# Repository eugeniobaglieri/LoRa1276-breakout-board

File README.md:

# LoRa1276-breakout-board
KiCad schematics and pcb of a breakout board adapter for Nicerf Lora1276 V2.0 - module.

In this Kicad project you will find:
- Nicerf LoRa1276 symbol schematics
- Nicerf LoRa1276 footprint
- Lora Breakout board Adapter schematics
- PCB file
- LORA1276-V2.2 module doc.pdf: Wich contains module specification and measures

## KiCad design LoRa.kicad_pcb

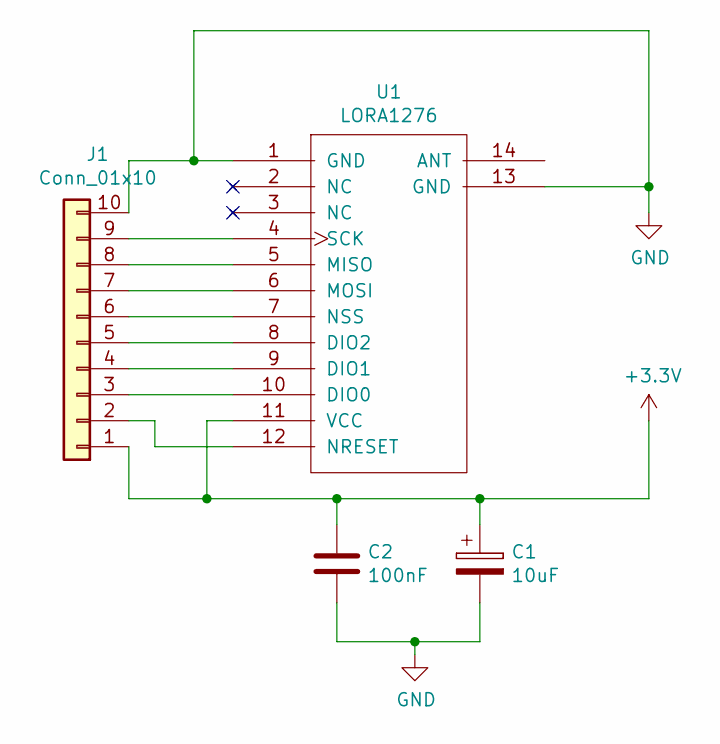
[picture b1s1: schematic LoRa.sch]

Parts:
C1: 10uF; CP_Radial_D5.0mm_P2.50mm
C2: 100nF; C_Disc_D3.8mm_W2.6mm_P2.50mm
J1: Conn_01x10; PinHeader_1x10_P2.54mm_Horizontal
U1: LORA1276

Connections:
+3V3: C1.1, C2.1, J1.1, U1.11 (VCC)
GND: C1.2, C2.2, J1.10, U1.1 (GND), U1.13 (GND)
unnamed: J1.2, U1.12 (NRESET)
unnamed: J1.3, U1.10 (DIO0)
unnamed: J1.4, U1.9 (DIO1)
unnamed: J1.5, U1.8 (DIO2)
unnamed: J1.6, U1.7 (NSS)
unnamed: J1.7, U1.6 (MOSI)
unnamed: J1.8, U1.5 (MISO)
unnamed: J1.9, U1.4 (SCK)

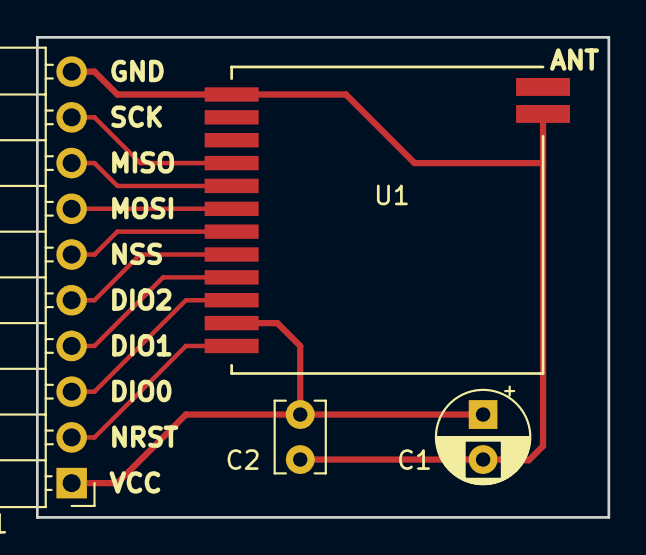
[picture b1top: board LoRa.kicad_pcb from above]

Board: 2 copper layers, 31.8 x 26.7 mm, 4 parts (0 on the bottom side), 10 nets.

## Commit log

2019-03-20 Project files added
2019-03-20 update README
    Images added
    Nicerf LoRa12476 doc pdf added
